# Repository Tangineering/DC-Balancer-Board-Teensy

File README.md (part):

# Scale_Car_Teensy

Teensy 4.1 firmware for a scale FCHEV (Fuel-Cell Hybrid EV) platform — the **Scale Car DC
Balancer Board, Rev 20260622**.

The board is a bidirectional power-pathing balancer: ideal-diode source switches route a fuel
cell and a 2S battery onto a shared VBUS, a regen path returns braking energy to the charger,
and an MPPT module harvests into the battery. This firmware drives that hardware.

It controls:
- motor torque through a VESC (`VescUart` over UART),
- fuel-cell/battery power sharing through dual AD5443 MDAC droop outputs (SPI),
- the RT1987 ideal-diode power-path switches (6 sequenced GPIOs),
- the Silvertel **Ag105** MPPT battery charger (I2C config + `MPPT_DISABLE` GPIO),
- the BQ29200 cell OVP/balancer (`CBAL_DISABLE` GPIO),
- command/telemetry with a Raspberry Pi over UDP Ethernet,
- a safety state machine, Pi watchdog, latching fault handling, and a USB-serial test mode.

> The authoritative hardware sources are `references/Scale Car Teensy IO - IO.csv` (pin map),
> `references/Scale Car Design PCB BOM 20260622.csv` (parts), and the schematic PDF. See
> `CLAUDE.md` for the reconciliation spec and `PLAN.md` for the implementation plan. For
> hardware-in-the-loop testing (a bare Teensy against a simulated plant, no PCB needed), see
> `docs/HIL_MODE.md` (protocol/architecture) and `docs/HIL_USER_MANUAL.md` (operator manual).

## Hardware interfaces

- **UART (`Serial1`)**: VESC motor controller (`RX`=0, `TX`=1).
- **SPI**: two AD5443 MDACs (`CS_MDAC_FC`=36, `CS_MDAC_BT`=37) for FC/BT droop gains; OPA197
  output buffers run from the 5 V rail (hardware bodge).
- **I2C (`Wire`)**: Silvertel **Ag105** charger at address **0x30**.
- **Ethernet/UDP**: command in (port 5001), telemetry out (port 5000), Teensy IP 192.168.1.50.
- **Encoder interrupts**: wheel-speed estimation from `ENC_A`=14 / `ENC_B`=15 (bodged from 2/8 on
  2026-08-16; the optical sensors are hardwired to power, so there is no enable pin).
- **ADC inputs (12-bit)**: FC/BT current (INA253A1, 0.1 V/A), FC/BT/BUS/CHG/RGN voltages.
- **Digital outputs**: FC/BT boost enables, 6 RT1987 path switches, `MPPT_DISABLE`,
  `CBAL_DISABLE`, encoder enable.

### Power-path switches (RT1987 ideal-diode controllers)

| Pin | Name | Role |
|----|------|------|
| 27 | `FC_BUS_ENABLE` | FC regulator → VBUS |
| 28 | `BT_BUS_ENABLE` | BT regulator → VBUS |
| 29 | `MOT_PWR_ENABLE` | VBUS → VESC/motor (Run only) |
| 30 | `REGEN_ENABLE` | regen → charger input |
| 31 | `FC_CHARGE_ENABLE` | VBUS(FC) → charger (guarded) |
| 32 | `BT_SEQUENCE_ENABLE` | battery-pack sequencing (init LOW, then HIGH) |

All switches default LOW at boot (fail-safe; 10 kΩ EN-to-GND bodge resistors back this up).
`FC_CHARGE_ENABLE` and `REGEN_ENABLE` are **mutually exclusive** and are only ever driven
through `assertFcChargeEnable()`, which forces `BT_BUS_ENABLE` and `REGEN_ENABLE` LOW (with an
RT1987 turn-off settle delay) before opening the FC→charger path.

**VBUS bring-up — only enable a boost on a stiff source.** The hazard is *not* bus inrush: VBUS
carries only ~30–40 µF (the RT1987 ceramics); the 470 µF bulk cap is on the V-MOT/regen node behind
`MOT_PWR_ENABLE`. The real failure mode is enabling a boost on a source that can **collapse**:
switching with built-up inductor current on a sagging/recovering rail destroys the power stage. The
exact mechanism is **unconfirmed pending a scope capture** — most likely a VOUT overshoot past the
20 V SW/VOUT abs-max (the TPS61288 OVP is at 19 V, only ~0.5 V of margin, and the 3×22 µF output
caps DC-derate to ~30 µF) and/or transient reverse conduction. Either way the destructive energy
comes from the boost's own inductor/output cap, so *a supply current limit does not bound it*. On a
board-powered Teensy this also motorboats: the boost loads `VBT`, the logic rail browns out, the MCU
resets, and re-enables the boost. So in **production** (`BENCH_TEST=0`, stiff vehicle source) State 0
brings the bus up gently (switches first, then the boosts' own soft-start) and is mirrored by the
State 98 `G` command; the bus is then kept energized through Idle/Finish so a Run never re-hot-plugs
it. Under **`BENCH_TEST`** State 0 keeps the power stage **off** at boot (see State 0 below). Bench
rule: the supply must exceed the logic baseline (≥ ~0.5–1 A) or the board-powered Teensy browns out,
and the bus may be brought up (`G`) only on a stiff supply.

## Runtime flow

Main loop execution order:
1. `updateSensors()`
2. `computeDerivedSignals()`
3. `detectFaults()`
4. `checkPiWatchdog()`
5. `receiveCommands()`
6. state machine (`doState0/1/2/3/98/99`)
7. `pollAg105()` + `sendTelemetry()` at ~50 Hz

## State machine

- **State 0 (Init)**: behavior depends on the `BENCH_TEST` build flag.
  - **Production (`BENCH_TEST=0`)**: a **non-blocking phase machine** that brings VBUS up gently —
    bus switches first (`FC_BUS_ENABLE`/`BT_BUS_ENABLE`), settle, then the FC/BT boosts (their
    soft-start raises the bus; see *VBUS bring-up* above). Raises `BT_SEQUENCE_ENABLE`, inits the
    MDAC and VESC, then **gates the transition to Idle on `V_bus ≥ V_BUS_CHARGED_THRESH`**; if the
    bus never reaches it within `BUS_CHARGE_TIMEOUT_MS`, raises `FAULT_INIT_FAIL` → State 99
    (catches a dead boost, failed switch, or no source).
  - **Bench (`BENCH_TEST=1`, the default flash)**: boots **straight to Idle with the power stage
    OFF** — boosts, bus switches, and `BT_SEQUENCE` all stay LOW, and there is no `V_bus` gate. This
    prevents enabling a boost on a soft/current-limited bench supply (which browns out the
    board-powered Teensy and motorboats the boost to failure). Bring the bus up manually with the
    State 98 `G` command on a stiff supply.
  - Either way the Ag105 is **not** configured here — it is unpowered in Init; `pollAg105()`
    configures it lazily once a charger path powers it. Shared init lives in `initControlPeripherals()`.
- **State 1 (Idle)**: motor current zero, `MOT_PWR_ENABLE` LOW; the bus is left **energized**
  (boosts + bus switches stay ON). Waits for a Run command from the Pi, or `T` on USB serial to
  enter test mode (State 98).
- **State 2 (Run)**: `MOT_PWR_ENABLE` HIGH; run `chargingControl()`, `motorControl()`,
  `powerBalance()`. `chargingControl()` owns the `REGEN`/`FC_CHARGE`/`BT_BUS` switches and the
  `MPPT_DISABLE` line. The bus is already up from Init/Idle, so entering Run does not hot-plug it.
- **State 3 (Finish)**: stops the motor and closes the motor/regen/charge paths, but **leaves the
  boosts + bus switches ON** so the bus stays armed and the next Idle→Run never re-hot-plugs the
  470 µF bus. Clears the wheel-speed buffer and returns to Idle. (No cap/regen drain — the
  disabled-boost back-feed hazard doesn't apply while the boosts stay enabled.)
- **State 98 (Test)**: USB-serial hardware exerciser (see below).
- **State 99 (Error)**: **non-blocking** two-phase safe shutdown that bleeds VBUS/regen energy and
  then disables the boosts and tears the bus down — latched until power cycle (which re-runs the
  State-0 gentle bring-up).

The State 99 shutdown is a phase machine gated on `millis()` (no blocking `delay()`), so
`detectFaults()` keeps sampling through the highest-energy drain windows.

## Charger control (Silvertel Ag105)

There is **no charge-current register to program per-mA**. Control is:
- **I2C config is LAZY, not at init** (`pollAg105()`): the charger is unpowered in
  Init/Idle (no charger power path is open, so it cannot ACK I2C), so reg `0x00 = 0x01`
  (2.5 A profile) and reg `0x01 = 0x08` (2S / 8.4 V) are written the first time
  `chargerHasPower()` is true and the `AG105_SETTLE_MS` bring-up window has elapsed and
  the charger ACKs. Stored in EPROM; the flag re-arms on power loss, so writes are
  idempotent. **fw v24** adds a dynamic reg `0x02` MPPT input-voltage threshold, written
  through the same power-gated lazy path with a read-verify-write handshake and an
  EPROM-wear write-rate budget.
- **`MPPT_DISABLE` GPIO (pin 5, active-LOW)**: LOW inhibits the MPPT loop (during regen,
  so it doesn't fight the fast transient); HIGH releases it (cruise/coast harvest). The
  Ag105's MPPT mechanism is an **input-voltage-threshold regulator** (datasheet p.10),
  not perturb-and-observe — charging commences only once the input exceeds a threshold
  set by reg `0x02` (11–33 V, ~0.088 V/count; default 18 V with no MPPTS resistor
  fitted).
- **I2C polling** (`pollAg105()` at 50 Hz): reads reg `0x06` (measured charge current,
  0.011 A/count) into `I_charge`, and caches the Table-6 status byte. The Ag105 prepends its
  status byte before any read, so each 1-byte field is read as 2 bytes.
- **Readiness** (`ag105IsReady()`): GENSTAT (status bits [2:0]) == Charging (0x02) or
  Fully Charged (0x03).
- An Ag105 I2C read failure only latches State 99 in the charging-relevant states (Run/Finish);
  in Init/Idle/Test a missing or still-powering charger does not lock the system.

## Telemetry & commands

- **Commands**: 22-byte UDP packet (sync `0xBB` + XOR checksum). Fields: timestamp, counter,
  `v_setpoint`, `power_share_setpoint`, `charge_goal`, `mode_cmd`, and a reserved `droop_enable`
  byte (parsed, not yet wired).
- **Telemetry — protocol v4, 58 bytes** (`TELEMETRY_VERSION = 4`, sync `0xAA`, XOR over bytes
  1–56). Carries the measured/derived signals, droop gains, the raw Ag105 Table-6
  `charger_status` byte (offset 51), a `switch_state` bitmask of the 6 path switches, a 16-bit
  `fault_flags`, the latched `error_code`, and `error_source_state`. The Pi bridge parses fixed
  offsets and **must match this version** — see `PLAN.md` §6b for the byte-by-byte layout and the
  block comment above `sendTelemetry()`.

## Key functions

### `motorControl()` + `PI_Controller_Motor()`
Computes torque from speed error (`v_setpoint - v_actual`) and commands VESC current. The
integrator has **anti-windup**: `pi_motor_accum` is clamped to the torque equivalent of
`MOTOR_I_CMD_MAX`. Integrator state is file-scope (resettable by the unit tests).

### `powerBalance()` + `PI_Controller_Power()`
Controls the FC/BT split from measured INA253 currents; PI output (`droopRatio`) is mapped to
FC/BT droop gains and written via `setDroopMdac()` (AD5443, SPI_MODE0, MSB-first, `transfer16`).

### `chargingControl()`
Manages `MPPT_DISABLE` and the regen/FC-charge/BT-bus switches based on `charge_goal`, regen
state (`current < -0.1`), and Ag105 readiness — enforcing the FC-charge/regen mutual exclusion.

### `updateWheelSpeed()` + encoder ISRs
An **edge-period estimator** (fw v12, hardened by the fractional-pitch ledger in fw v15/v17)
measures the period between same-edge-type quadrature transitions to derive flywheel speed →
`v_actual`. It replaced the original boxcar (fixed-window sample-counting) estimator, whose
~113 ms window realized enough group delay to limit-cycle the drive loop at its own crossover.
Direction comes from the quadrature decode; a ring-invalidation event on a direction flip
holds the last valid reading (bounded by a stale timeout) rather than emitting a full-scale
zero step. State 3 resets the estimator between runs so a new run's first samples aren't
measured against stale timestamps.

## Safety features

- FC overcurrent (`I_fc > LIMIT_I_FC_MAX`), BT overcurrent (`I_batt > LIMIT_I_BT_MAX`)
- Battery UV/OV, FC UV — **UV checks are gated to Run (State 2)** so unramped rails at boot
  don't latch State 99
- Bus OV (`LIMIT_V_BUS_MAX = V_BUS_NOMINAL + 1.5 = 17.5 V` at the 16.0 V nominal, below the 19 V TPS61288 HW OVP) and Bus UV (Run only)
- Regen-node and charger-input overvoltage
- Illegal switch combination (`FC_CHARGE_ENABLE` with `BT_BUS`/`REGEN`)
- Ag105 GENSTAT error states (OC/Regulation 0x05, Thermal Shutdown 0x06, Timeout 0x07) and I2C
  comms failure
- Pi watchdog timeout (`PI_TIMEOUT_MS`, States 2/3 only)

Faults funnel through `triggerFault()`, which latches a primary `error_code` + source state and
transitions to **State 99**.

## Fault reference

When any check in `detectFaults()` trips, `triggerFault()` sets that condition's bit in the
16-bit `fault_flags`, latches the **first** cause into `error_code` (and the active state into
`error_source_state`), forces `FAULT_ERROR` (`0x8000`), and transitions to **State 99** —
latched until power cycle. Both `fault_flags` and `error_code` ride in the v4 telemetry packet,
so every value below is observable on the Pi. Read `error_code` for the root cause and
`fault_flags` for everything that tripped.

### Fault flags (`fault_flags` bitmask)

`fault_flags` is an OR of these bits — more than one can be set at once:

| Mask | Flag | Trigger | Limit | Gated to |
|------|------|---------|-------|----------|
| `0x0001` | `FAULT_OC_FC` | `I_fc` overcurrent | `LIMIT_I_FC_MAX = 3.5 A` | all |
| `0x0002` | `FAULT_UV_BATT` | `V_batt` undervoltage | `LIMIT_V_BATT_MIN = 6.2 V` | Run |
| `0x0004` | `FAULT_OV_BUS` | `V_bus` overvoltage | `LIMIT_V_BUS_MAX = 17.5 V` | all |
| `0x0008` | `FAULT_SWITCH_CONFLICT` | `FC_CHARGE_ENABLE` high while `BT_BUS`/`REGEN` high | — | all |
| `0x0010` | `FAULT_PI_TIMEOUT` | Pi watchdog expired | `PI_TIMEOUT_MS` | States 2/3 |
| `0x0020` | `FAULT_OV_BATT` | `V_batt` overvoltage | `LIMIT_V_BATT_MAX = 8.6 V` | all |
| `0x0040` | `FAULT_UV_FC` | `V_fc` undervoltage | `LIMIT_V_FC_MIN = 6.0 V` | Run |
| `0x0080` | `FAULT_OC_BT` | `I_batt` overcurrent | `LIMIT_I_BT_MAX = 6.0 A` | all |
| `0x0100` | `FAULT_UV_BUS` | `V_bus` undervoltage | `LIMIT_V_BUS_MIN = 12.0 V` | Run |
| `0x0200` | `FAULT_OV_RGN` | regen-node overvoltage | `LIMIT_V_RGN_MAX = 28.0 V` | all |
| `0x0400` | `FAULT_OV_CHG` | charger-input overvoltage | `LIMIT_V_CHG_MAX = 24.0 V` | all |
| `0x0800` | `FAULT_I2C_CHARGER` | Ag105 I2C comms failure | — | Run/Finish |
| `0x1000` | `FAULT_CHARGER_STAT` | Ag105 GENSTAT error (`0x05` OC/regulation, `0x06` thermal, `0x07` timeout) | — | charging states |
| `0x2000` | `FAULT_INIT_FAIL` | init failure: VBUS failed to reach `V_BUS_CHARGED_THRESH` within `BUS_CHARGE_TIMEOUT_MS` (also legacy Ag105 config) | `V_BUS_CHARGED_THRESH` | State 0 |
| `0x8000` | `FAULT_ERROR` | latched marker: system entered State 99 | — | set with any fault |

The UV checks marked **"Gated to Run"** are deliberately suppressed outside State 2, so unramped
rails at boot don't latch State 99 (see Safety features above).

### Error codes (`error_code` latched cause)

`error_code` is the single latched primary cause — the *first* fault to fire — and is distinct
from the multi-bit `fault_flags`. `error_source_state` records which state was active when it
latched. Values map 1:1 to `errorCodeStr()`:

| Code | Enum | String |
|------|------|--------|
| `0x00` | `ERR_NONE` | (none) |
| `0x01` | `ERR_OC_FC` | FC overcurrent |
| `0x02` | `ERR_UV_BATT` | Batt undervoltage |
| `0x03` | `ERR_OV_BUS` | Bus overvoltage |
| `0x04` | `ERR_SWITCH_CONFLICT` | Switch conflict |
| `0x05` | `ERR_PI_TIMEOUT` | Pi timeout |
| `0x06` | `ERR_OV_BATT` | Batt overvoltage |
| `0x07` | `ERR_UV_FC` | FC undervoltage |
| `0x08` | `ERR_OC_BT` | BT overcurrent |
| `0x09` | `ERR_UV_BUS` | Bus undervoltage |
| `0x0A` | `ERR_OV_RGN` | Regen overvoltage |
| `0x0B` | `ERR_OV_CHG` | Charger input OV |
| `0x0C` | `ERR_I2C_CHARGER` | Ag105 I2C fail |
| `0x0D` | `ERR_CHARGER_STAT` | Ag105 STAT fault |
| `0x0E` | `ERR_INIT_FAIL` | Init failure |

**Recovery:** State 99 is latched — a fault clears only on a power cycle. Diagnose with
`error_code` (root cause) first, then inspect the full `fault_flags` bitmask for any secondary
conditions that tripped in the same tick.

## Test mode (State 98)

State 98 is a USB-serial hardware exerciser for bench bring-up. **Enter** it by sending `T`
while in Idle (State 1); **exit** with `Q`, which returns to Idle and forces `MOT_PWR_ENABLE`
LOW. The Pi watchdog is suspended in this state, but `detectFaults()` still runs every tick — a
fault latches State 99 exactly as in normal operation. `FC_CHARGE_ENABLE` only ever moves through
`assertFcChargeEnable()`, even here.

### Serial command set

All commands are single characters over USB serial; every toggle echoes the resulting pin state
back over serial:

| Key | Action | Notes |
|-----|--------|-------|
| `F` | Toggle `FC_REG_ENABLE` (FC boost) | |
| `B` | Toggle `BT_REG_ENABLE` (BT boost) | |
| `1` | Toggle `FC_BUS_ENABLE` | **ON refused** if FC boost is ON and `V_bus` < `V_BUS_CHARGED_THRESH` (hot-plug guard — use `G`) |
| `2` | Toggle `BT_BUS_ENABLE` | same hot-plug guard as `1`; **also refused** while `FC_CHARGE_ENABLE` is HIGH (illegal combination) |
| `3` | Toggle `MOT_PWR_ENABLE` | ON allowed **only at a regulated bus** (`motPwrConnectBlocked()`); must be HIGH before `D`/`R` |
| `4` | Toggle `REGEN_ENABLE` | forces `FC_CHARGE` off via `assertFcChargeEnable(false)` before going HIGH |
| `5` | Toggle `FC_CHARGE_ENABLE` | always through the `assertFcChargeEnable()` guard |
| `6` | Toggle `BT_SEQUENCE_ENABLE` | |
| `C` | Toggle `CBAL_DISABLE` | HIGH = OVP bypassed (prints a warning) |
| `M` | Toggle `MPPT_DISABLE` | HIGH = MPPT harvesting; LOW = inhibited |
| `N` | Dynamic Ag105 MPPT reg-`0x02` threshold status/verify (fw v24) | read-verify-write handshake against the EPROM-wear write-rate budget; see `CLAUDE.md`'s 2026-09-01a addendum |
| `G` | Staged bus bring-up | `busBringupTick()` phases P0–P3: bus alone → boosts → dwell → motor node; `X` aborts (stage dark) |
| `D` | Start/stop simulated drive cycle | requires `MOT_PWR_ENABLE` HIGH and the calibrated velocity chain |
| `S` | Print status dump (all pins, ADCs, `I_charge`, faults, bench-tool state) | read-only |
| `I` | Scan the I2C bus | read-only |
| `E` | One-shot VESC firmware + telemetry read | blocks up to ~100 ms (bench-only) |
| `U` | Toggle VESC watch (~2 Hz `[VW]` line, flags fault changes) | **rebound from `W` (2026-08-10)**; auto-paused during profiles and plot mode |
| `P` | Set power-share setpoint (prompts for a value) | closed-loop: `powerBalance()` drives the MDACs live; needs current flowing |
| `O` | Set droop ratio 0.15–0.85 (prompts for a value) | open-loop direct MDAC write; no current needed — the calibration entry point |
| `A` | Set manual motor current in A (prompts) | constant VESC current, bypasses the drive controller |
| `V` | Set manual motor velocity in m/s (prompts) | refused until the velocity chain is calibrated |
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
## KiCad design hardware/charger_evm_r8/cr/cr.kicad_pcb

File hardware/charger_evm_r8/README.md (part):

# Charger EVM r9: design review guide

## 1. Purpose and how to read this document

This README presents the r9 charger design for operator review, with progressive detail. Section 2 shows the overall
functional block diagram and the architecture. Section 3 lists what changed on 2026-11-12; a reader who needs only the
changes can read section 3 alone. Sections 4 to 7 explain the design concepts, the permit gate, the operating modes and the
firmware consequences. Sections 8 to 12 cover the physical implementation, status, plan, open items and the source
index. Appendix A defines the abbreviations and the identifier families.

The full record is the design document `docs/charger_bq25798_wiring_design_2026-11-05.md` (revision r9). Section 12 maps
each topic to its authoritative file and section. Neither text that the design document marks "superseded", "withdrawn"
or "history" nor the r7-outline work in `archive_r7_outline/` is the current design.

## 2. Architecture

### 2.1 Block diagram

Three different parts carry the refdes J1. In this document, **CR J1** is the 22-pin CHG header (TSW strips). **MB
J1/J2** are the Teensy 4.1 Dubox receptacles, and **EVM J1** is the charger VIN screw terminal.

Figure 2.1 shows the power and signal architecture of the charger path. Power flows from VBUS or V-MOT into the EVM and
returns to the pack through CR J1 pads 18/19.

Figure 2.1. Charger path, block diagram (r9).

The diagram is schematic and not to scale. Thick red conductors carry power and thin blue lines carry logic or analog
signals; a bridge marks a crossing with no connection. The source is `gen/readme_figures.py`. Only CR J1 pad 11 and the J-TAP conductors enter the permit gate. Table 2.2, section 8.6 and
design-document sections A.5 and C give the EIB-to-EVM leads and the EVM modifications.

### 2.2 Blocks

Table 2.1 lists each block, its role and its physical location.

Table 2.1. Blocks of the charger path.

| Block | Role | Physical location |
|---|---|---|
| MB RT1987 switches D-BC-FC, D-BC-RG | Route VBUS (FC charging) or V-MOT (regen) into VCHG-IN | MB, existing parts |
| MB D-BT-SQ (RT1987) | Connects the charger output net VCHG to the pack VBT | MB, existing part |
| CR J1 (22-pin CHG header) | Mates the CR to the 22 former Ag105 holes | CR underside, TSW strips in MB SSQ sockets |
| eFuse U101 TPS26630RGER | Input current limit 2.23 A nominal, UVLO 9.91 V, OVP 23.12 V; fault output and IMON | CR top |
| Permit gate | Four comparators and five LVC packages; holds the converter off unless a release term is true | CR top |
| J-TAP (J102) | Brings the ten tap conductors onto the CR | CR, THT header, +x side |
| EVM (BQ25798) | Buck-boost charger, I2C address 0x6B | Off-board, on an insulating plate fixed to the chassis |
| EIB | Converts CR logic levels into /CE, ILIM_HIZ hold/release and the FC current clamp at the EVM | 2-layer board on two M3 x 10 mm nylon standoffs on the EVM plate |
| Teensy 4.1 | Commands CHG_ARM, CHG_QUAL and the RT1987 enables; reads readbacks and I2C | MB, on J1/J2 receptacles |

Every block in Table 2.1 appears in Figure 2.1. Only the MB switches, the eFuse and the EVM carry charger power; the
other blocks carry logic.

### 2.3 Interfaces

Table 2.2 lists each interface, its connector and what crosses it.

Table 2.2. Interfaces of the charger path.

| Interface | Connector | What crosses it |
|---|---|---|
| MB to CR power and signals | MB SSQ-110/112-01-L-S sockets, CR TSW-110/112-07-L-S strips (CR J1) | Pad 10 VCHGIN; pads 18/19 VCHG; pads 4, 14, 15 GND; pad 11 CHG_ARM; pad 3 STAT; pads 8/7 SDA/SCL; pad 13 TS_EXT; 11 pads without a net |
| MB to CR taps | J-TAP (J102) Micro-Fit 3.0 2 x 5 (Molex 43045-1012), cable Molex 2147561101 | T1, T7b, T2, T5, T6, T10, T13, T16, T17, T17r |
| CR to EVM input | W1 (VCHGOUT), W2 (GND); CR plated holes to EVM J1 screw terminal | Charger input, <= 2.41 A for <= 202 ms (eFuse limit), normally <= 1.76 A |
| EVM to CR output | W3 (VCHG), W4 (GND); EVM J5 screw terminal to CR plated holes | Charger output, <= 3.21 A |
| CR to EVM I2C | W7 twisted triple; CR plated holes to EVM J8 (Molex KK 254 housing) | SCL, SDA; GND bonded at the CR end only |
| CR to EVM thermistor | W6 twisted pair to EVM J7 pin 1 | TS_EXT; fitted only if a pack NTC is fitted at J-NTC |
| CR to EIB | W5 14-way 0.635 mm flat cable, CR J101 to EIB J201 | 3V3 (two conductors), CE_DRV, ILIM_REL_A, ILIM_REL_B, RFC_OFF to the EIB; STAT to the CR; four GND |
| EIB to EVM | E leads, 28 AWG Kynar | E8 AGND to TP49, E3 to TP33, E2 to JP14 pin 2, E7 STAT to TP38, E1 REGN to JP12, E5 /CE to TP36 |

Every interface in Table 2.2 appears in Figure 2.1. The power interfaces are CR J1 pads 4, 10, 14, 15, 18 and 19 and the
leads W1-W4. All logic crosses CR J1, J-TAP, W5, W6, W7 or the E leads.

## 3. What changed on 2026-11-12

The thermocouple and the polyimide sheet are removed, T-F-16 is retired, and no charging of any kind runs before the R5 build flag
(section 7.2). Sections 3.1 to 3.3 give the full change record.

### 3.1 Physical and functional changes

The 2026-11-12 decisions removed parts, moved signals and replaced the carrier outline. Table 3.1 lists every change that
a reviewer could otherwise miss. The decision identifiers refer to `LAYOUT_DECISIONS.md` (D-38 to D-50) and to the
design-document change rows r8-17 and r9-1 to r9-8. The CR outline row and the standoffs row also give the 2026-11-13
outline trim and mounting holes of D-60, as amended by the D-62 outline. (**Superseded 2026-11-13, D-62:** "outline
trim and mounting holes of D-60.")

Table 3.1. Changes of 2026-11-12.

| Area | Before (r8 or r7) | Now (r9) | Record |
|---|---|---|---|
| Thermocouple on the MB VBT trace | Fitted under the polyimide sheet, read in T-F-16 | **Removed.** No replacement. The MB VBT trace, at its IPC-2221 10 C rise at 3.21 A on 1 oz, is accepted unmeasured; T-F-16 is retired (operator ruling 2026-11-12, design-document J.1 item 25) | D-43 |
| Polyimide sheet over 368 untented MB vias | 0.125 mm sheet bonded under the CR | **Retired.** Protection is the >= 1.5 mm air gap and the solder-masked L4 GND | D-43 |
| CR outline | r7 outline with tab X, tab Y, chamfer and feet FT1/FT2 | **Plug-on rectangle** x 18.584-67, y 7-94 (48.416 x 87 mm, 4212.2 mm2), removable; this rectangle stays the placement frame. 2026-11-13: after routing, the board is trimmed to the **D-62 outline** inside the rectangle: 10 corners, edges at 0, 30, 45, 60, 90, 120, 135 or 150 degrees, slanted edges of at least 2.0 mm, 1.0 mm corner fillets; 2327.7 mm2 (55 %), bounding box 40.02 x 64.81 mm, x 18.584-58.60, y 7.83-72.64. (**Superseded 2026-11-13, D-62:** "a **convex 18-vertex outline** inside the rectangle: 2241.6 mm2 (53 %) ... x 18.58-58.60", the D-60 trim.) | D-39, D-60, D-62 |
| MB parts under the CR | None of the switching parts | Both boost switching nodes, L-FC, L-BT, REG-5V: about 1.6-3.3 W, BT boost TODO(calc) (Table 8.1) | D-39 |
| MB-CR mating | TSW pins soldered into the MB | Samtec SSQ sockets on the MB, TSW strips on the CR, hard stop at 11.05 mm | D-41 |
| Standoffs, feet, key | Feet FT1/FT2 bonded with RTV | **No standoffs on the MB.** Friction fit of 22 contacts; J-BL and J-FC stop a flipped CR, and a +x key ear keeps that overlap; T-F-18 re-scoped to CR retention. 2026-11-13: four 6-32 NPTH holes MH1-MH4 on the CR hold a 3D-printed support. (**Superseded 2026-11-13, D-60:** "**None.**" and "the terminal blocks stop a flipped CR".) | D-41, D-42, D-60 |
| Assembly | SMT on both sides | **All SMT on the top**, one stencil, one reflow; THT hand-soldered last | D-44 |
| Copper weight | 2 oz outer / 1 oz inner | 1 oz outer / 0.5 oz inner (OSH Park); set on 2026-11-11, kept by the 2026-11-12 amendment | D-29 |
| L4 use | Signals, the VCHGOUT strap and a GND pour | Solid GND, no signals, no straps | D-20 |
| Finish method | Interactive finish from the r7 start board | Retired; full route-race on the new outline | D-36, D-50 |
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
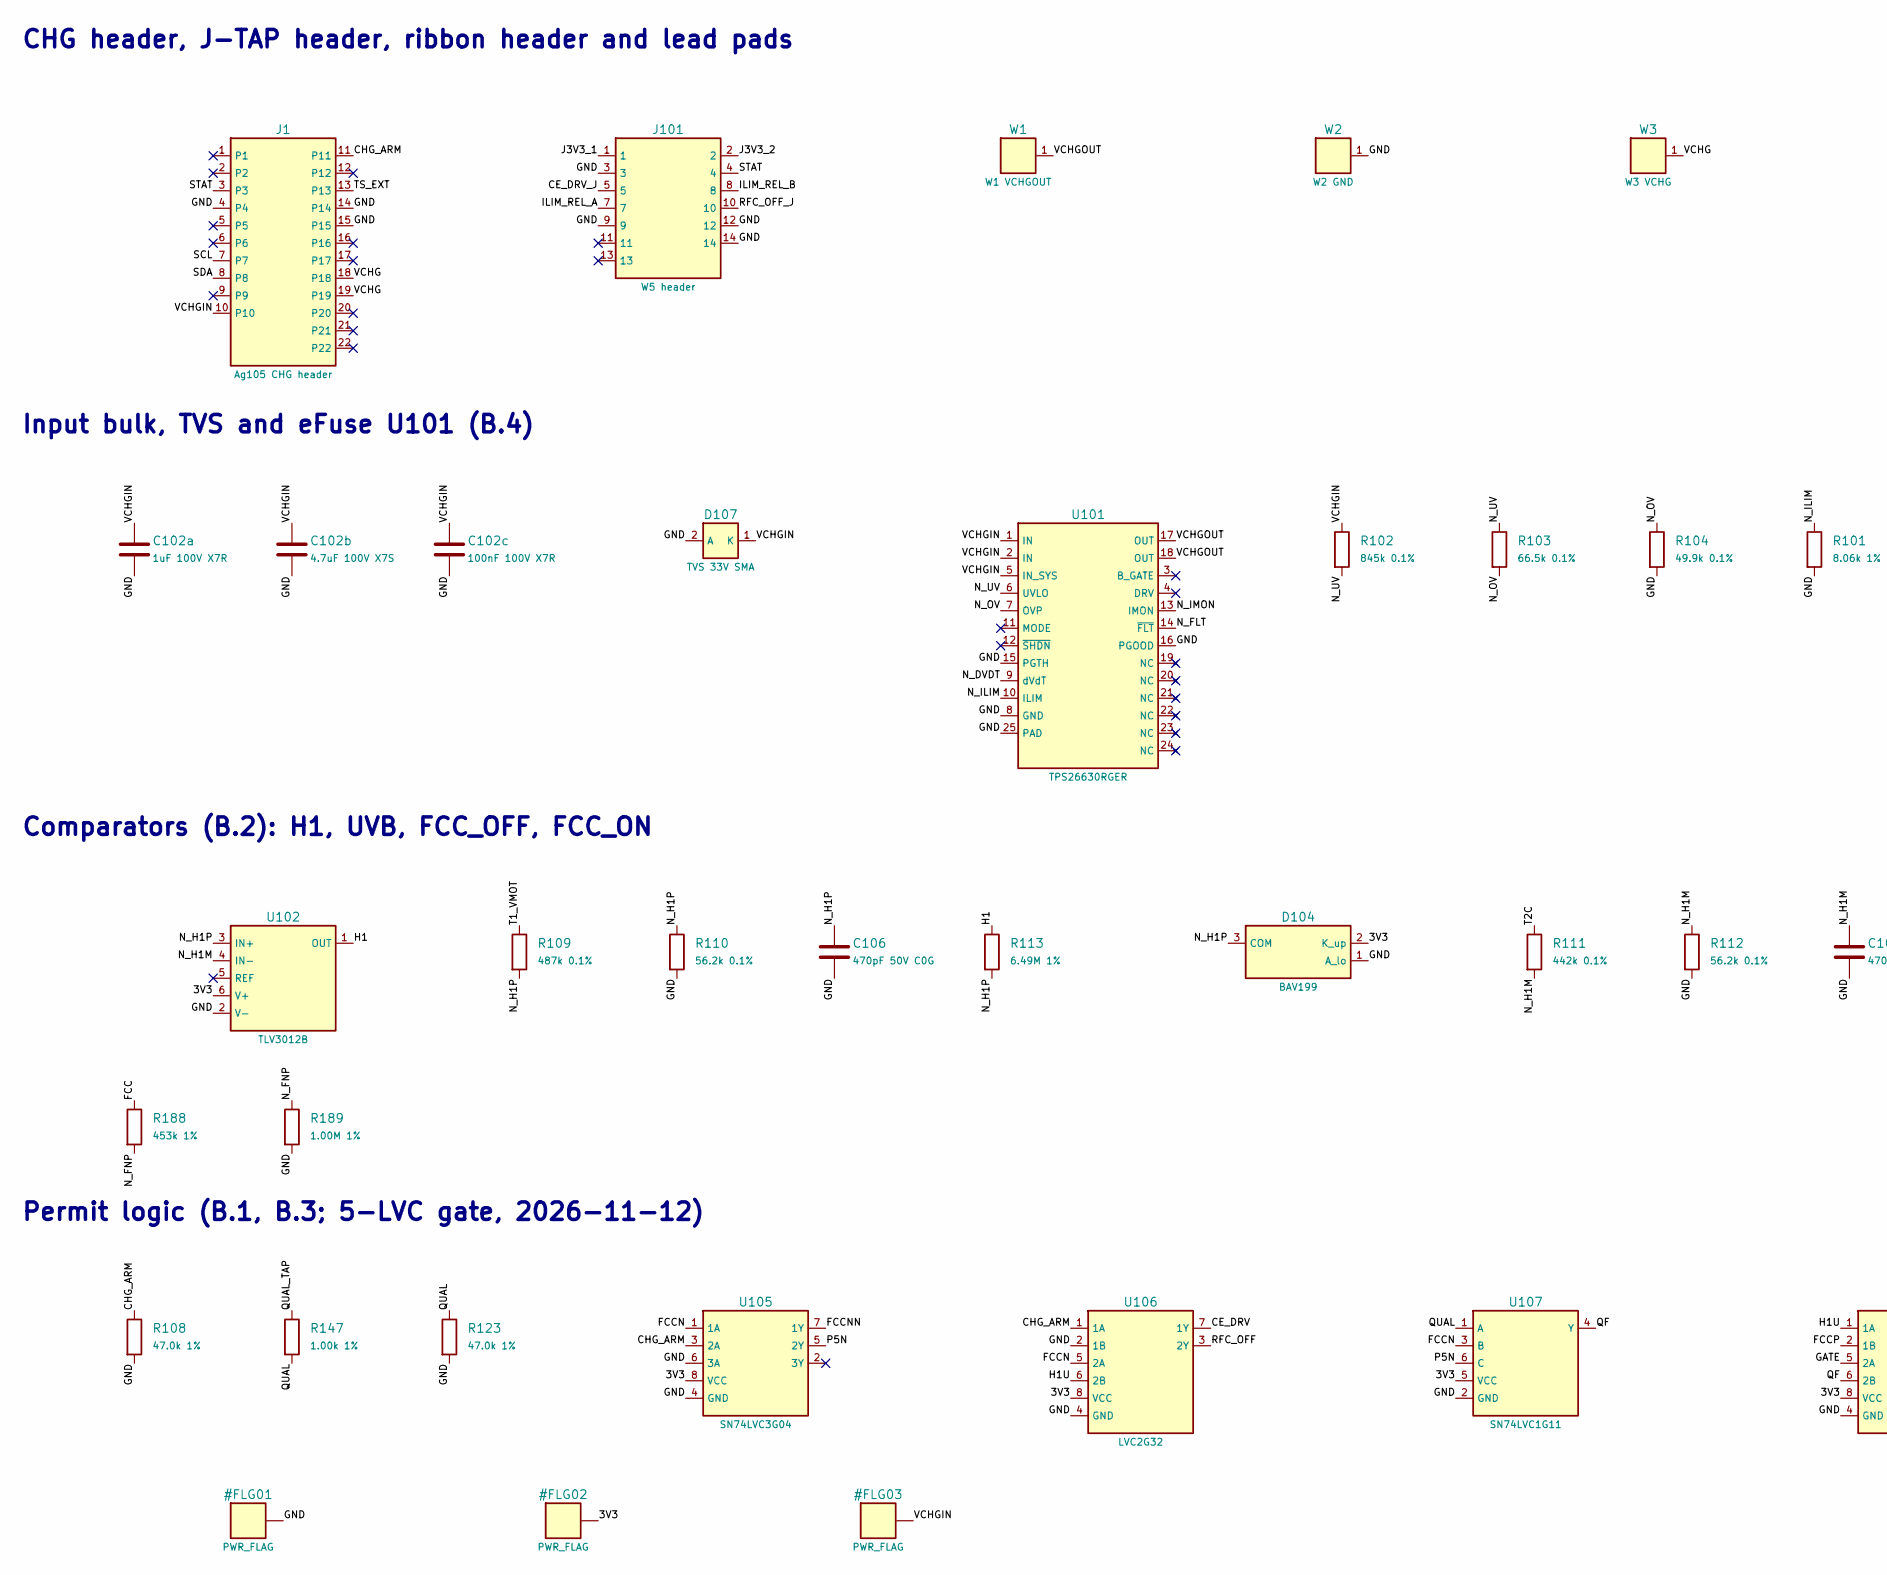
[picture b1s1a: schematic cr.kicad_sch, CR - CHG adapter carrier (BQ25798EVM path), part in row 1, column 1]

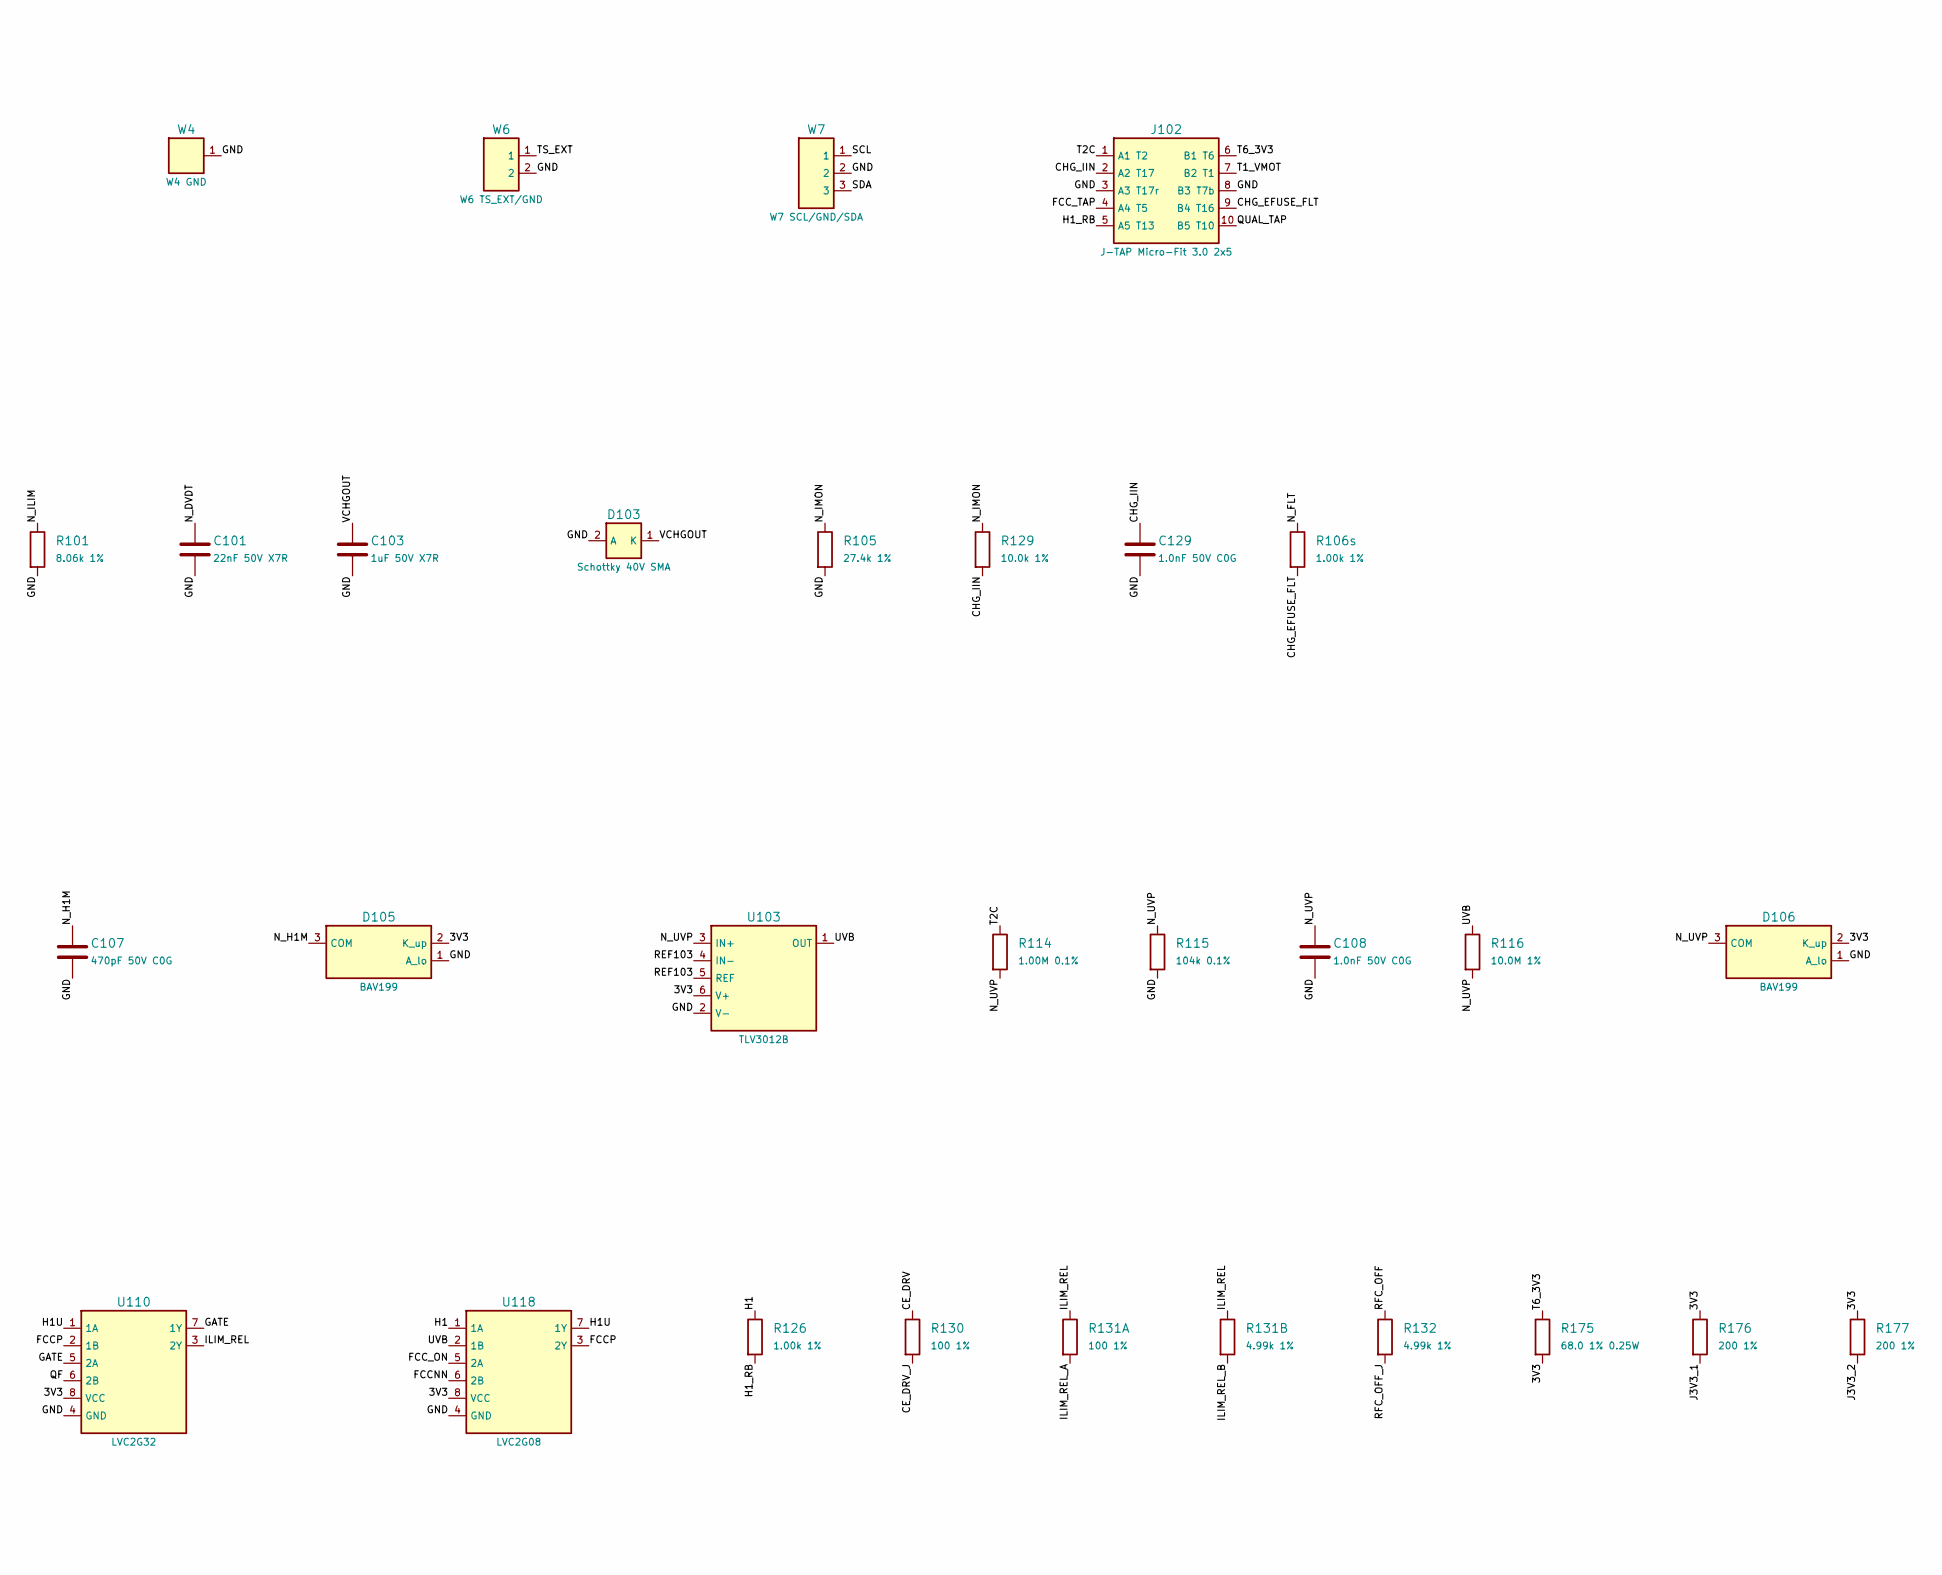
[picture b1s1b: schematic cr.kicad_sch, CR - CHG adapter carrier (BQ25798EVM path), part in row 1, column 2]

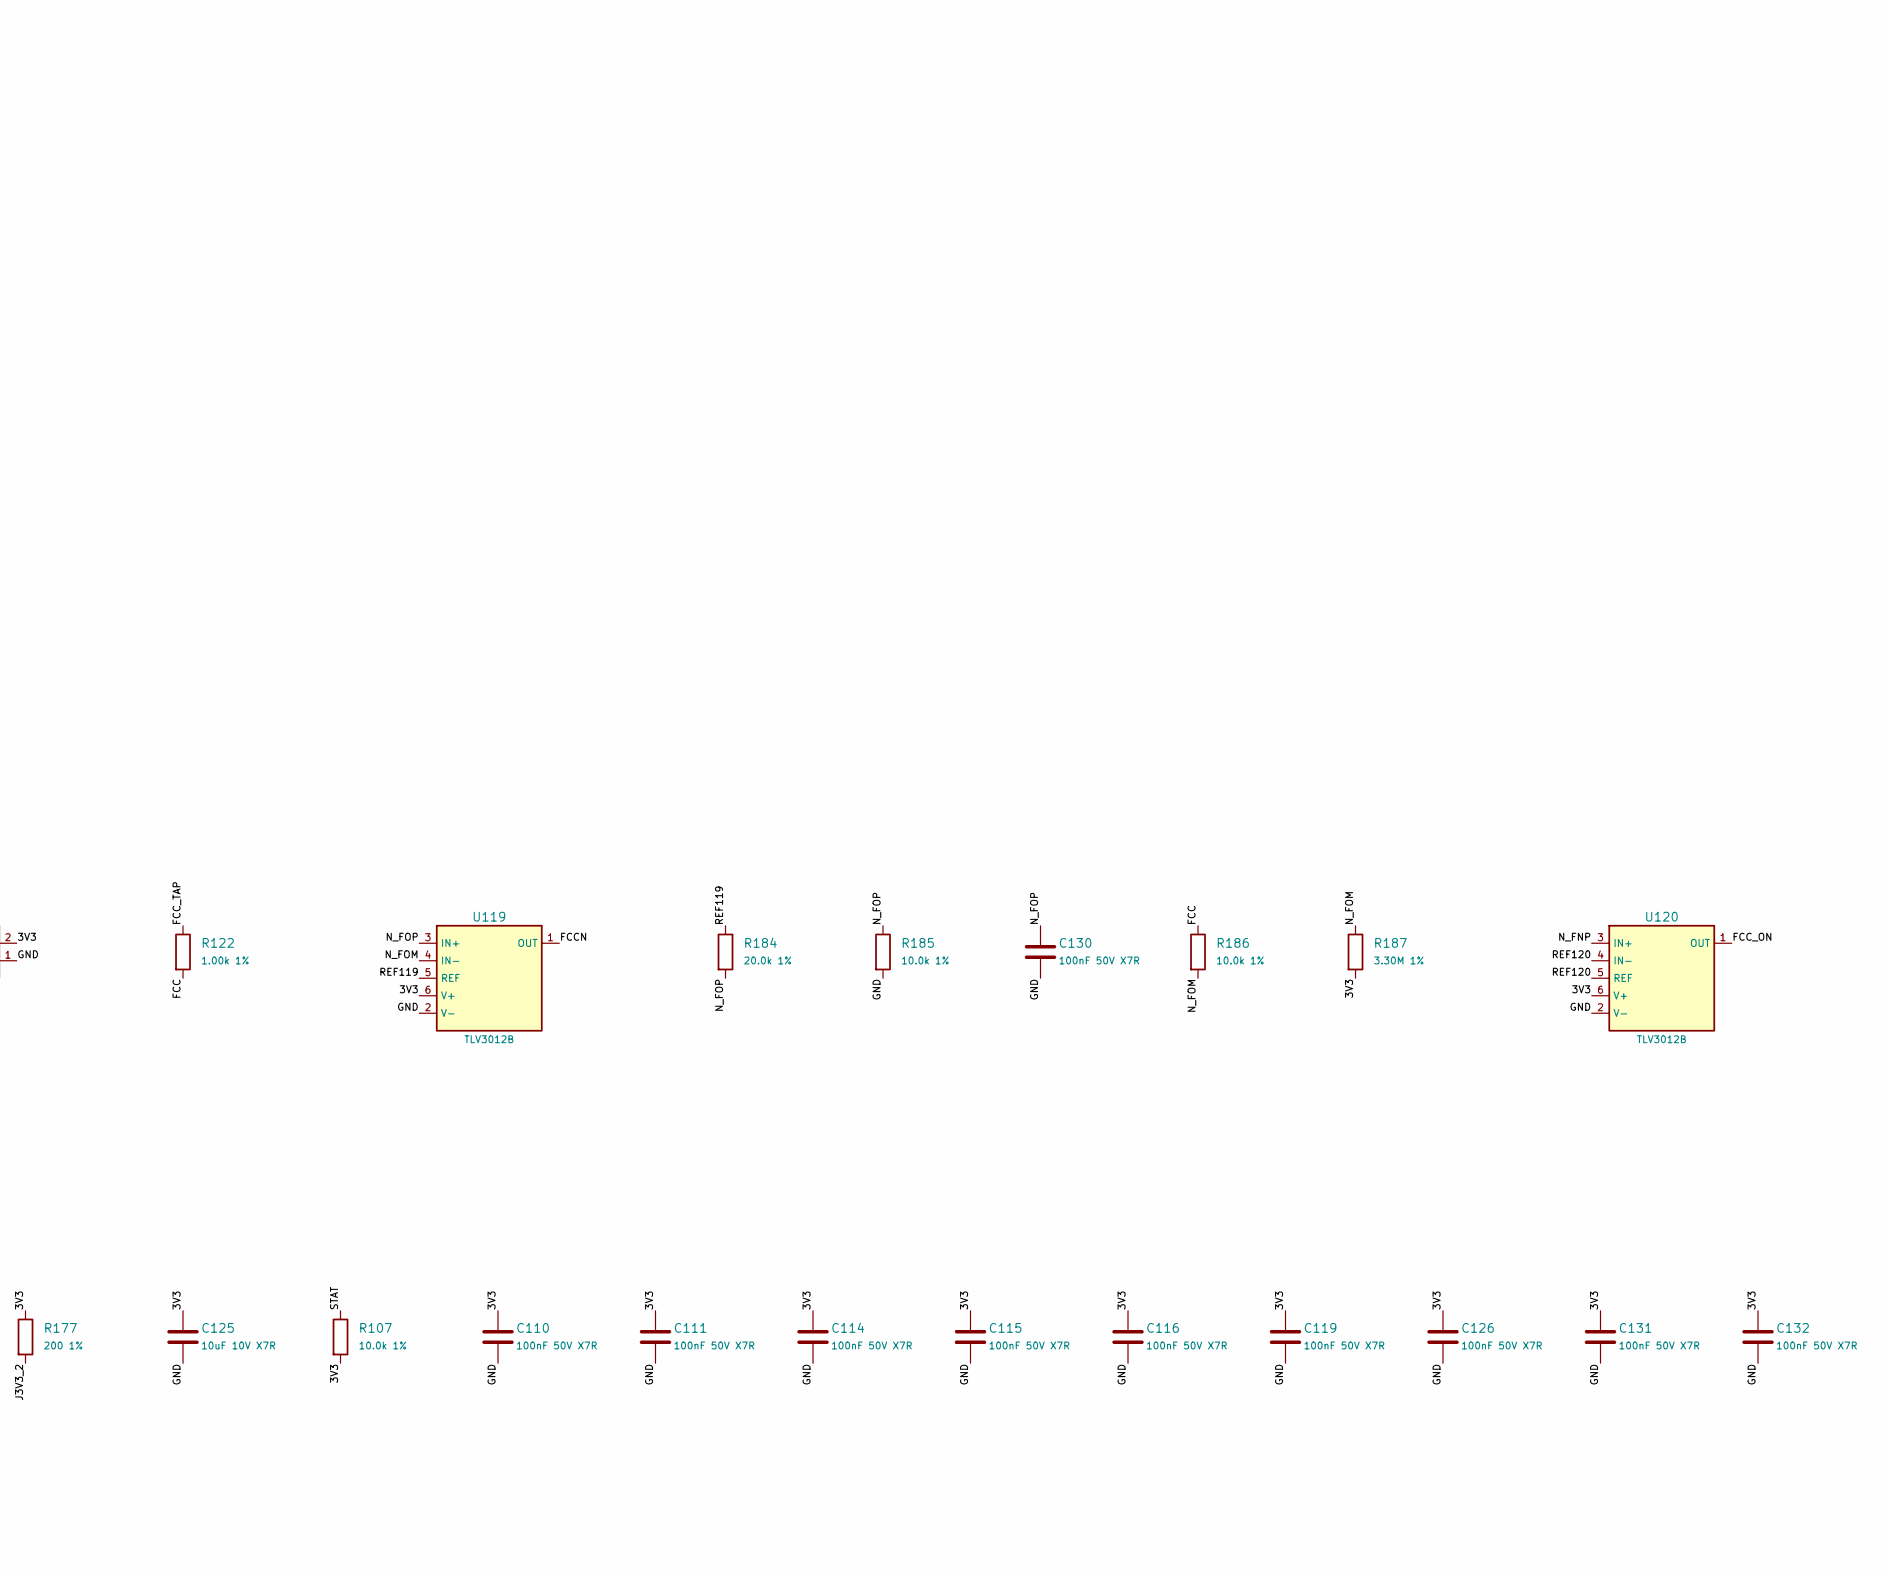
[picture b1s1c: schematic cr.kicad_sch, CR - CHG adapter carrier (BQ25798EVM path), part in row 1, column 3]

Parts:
C101: 22nF 50V X7R; C_0603_1608Metric_CrtYd0.25; MPN GRM188R71H223KA01D
C102a: 1uF 100V X7R; C_1206_3216Metric_CrtYd0.25; MPN GRM31CR72A105KA01L
C102b: 4.7uF 100V X7S; C_1210_3225Metric_CrtYd0.25; MPN C3225X7S2A475K
C102c: 100nF 100V X7R; C_0603_1608Metric_CrtYd0.25; MPN GRM188R72A104KA35D
C103: 1uF 50V X7R; C_0805_2012Metric_CrtYd0.25; MPN GRM21BR71H105KA12L
C106, C107: 470pF 50V C0G; C_0603_1608Metric_CrtYd0.25; MPN GRM1885C1H471JA01D
C108, C129: 1.0nF 50V C0G; C_0603_1608Metric_CrtYd0.25; MPN GRM1885C1H102JA01D
C110, C111, C114, C115, C116, C119, C126, C130, C131, C132: 100nF 50V X7R; C_0603_1608Metric_CrtYd0.25; MPN GRM188R71H104KA93D
C125: 10uF 10V X7R; C_0805_2012Metric_CrtYd0.25; MPN GRM21BR71A106KE51L
D103: Schottky 40V SMA; D_SMA_CrtYd0.25; MPN selected in T-A-05 (bench fallback B340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
D104, D105, D106: BAV199; SOT-23_CrtYd0.25; MPN BAV199,215
D107: TVS 33V SMA; D_SMA_CrtYd0.25; MPN SMAJ33A (candidate, T-A-05)
J1: Ag105 CHG header; Ag105_CHG_Carrier_22pin_P2.54mm; MPN TSW-110-07-L-S + TSW-112-07-L-S
J101: W5 header; Samtec_FTSH-107-01-DV_2x07_P1.27mm_SMD_NoPin6_CrtYd0.25; MPN FTSH-107-01-L-DV class (T-A-05)
J102: J-TAP Micro-Fit 3.0 2x5; Molex_Micro-Fit_3.0_43045-1012_2x05_P3.00mm_Vertical_CrtYd0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; MPN Molex Micro-Fit 3.0 2x5 THT header, 430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
R101: 8.06k 1%; R_0603_1608Metric_CrtYd0.25; MPN CRCW06038K06FKEA
R102: 845k 0.1%; R_0805_2012Metric_CrtYd0.25; MPN TNPW0805845KBEEA
R103: 66.5k 0.1%; R_0603_1608Metric_CrtYd0.25; MPN TNPW060366K5BEEA
R104: 49.9k 0.1%; R_0603_1608Metric_CrtYd0.25; MPN TNPW060349K9BEEA
R105: 27.4k 1%; R_0603_1608Metric_CrtYd0.25; MPN CRCW060327K4FKEA
R106s, R122, R126, R147: 1.00k 1%; R_0603_1608Metric_CrtYd0.25; MPN CRCW06031K00FKEA
R107, R129, R185, R186: 10.0k 1%; R_0603_1608Metric_CrtYd0.25; MPN CRCW060310K0FKEA
R108, R123: 47.0k 1%; R_0603_1608Metric_CrtYd0.25; MPN CRCW060347K0FKEA
R109: 487k 0.1%; R_0805_2012Metric_CrtYd0.25; MPN TNPW0805487KBEEA
R110, R112: 56.2k 0.1%; R_0603_1608Metric_CrtYd0.25; MPN TNPW060356K2BEEA
R111: 442k 0.1%; R_0805_2012Metric_CrtYd0.25; MPN TNPW0805442KBEEA
R113: 6.49M 1%; R_0603_1608Metric_CrtYd0.25; MPN CRCW06036M49FKEA
R114: 1.00M 0.1%; R_0805_2012Metric_CrtYd0.25; MPN TNPW08051M00BEEA
R115: 104k 0.1%; R_0603_1608Metric_CrtYd0.25; MPN TNPW0603104KBEEA
R116: 10.0M 1%; R_0603_1608Metric_CrtYd0.25; MPN CRCW060310M0FKEA
R130, R131A: 100 1%; R_0603_1608Metric_CrtYd0.25; MPN CRCW0603100RFKEA
R131B, R132: 4.99k 1%; R_0603_1608Metric_CrtYd0.25; MPN CRCW06034K99FKEA
R175: 68.0 1% 0.25W; R_1206_3216Metric_CrtYd0.25; MPN CRCW120668R0FKEA
R176, R177: 200 1%; R_0603_1608Metric_CrtYd0.25; MPN CRCW0603200RFKEA
R184: 20.0k 1%; R_0603_1608Metric_CrtYd0.25; MPN CRCW060320K0FKEA
R187: 3.30M 1%; R_0603_1608Metric_CrtYd0.25; MPN CRCW06033M30FKEA
R188: 453k 1%; R_0603_1608Metric_CrtYd0.25; MPN CRCW0603453KFKEA
R189: 1.00M 1%; R_0603_1608Metric_CrtYd0.25; MPN CRCW06031M00FKEA
U101: TPS26630RGER; TPS26630_RGE0024_VQFN-24_4x4mm_P0.5mm_ThermalVias_CrtYd0.25; MPN TPS26630RGER
U102, U103, U119, U120: TLV3012B; SOT-23-6_CrtYd0.25; MPN TLV3012BIDBVR
U105: SN74LVC3G04; Texas_DCT0008A_SSOP-8_TI-land_CrtYd0.25; MPN SN74LVC3G04DCTR
U106, U110: LVC2G32; Texas_DCT0008A_SSOP-8_TI-land_CrtYd0.25; MPN SN74LVC2G32DCTR
U107: SN74LVC1G11; SOT-23-6_CrtYd0.25; MPN SN74LVC1G11DBVR
U118: LVC2G08; Texas_DCT0008A_SSOP-8_TI-land_CrtYd0.25; MPN SN74LVC2G08DCTR
W1: W1 VCHGOUT; LeadPad_PTH_D1.3mm_Pad2.3mm_CrtYd0.25
W2: W2 GND; LeadPad_PTH_D1.3mm_Pad2.3mm_CrtYd0.25
W3: W3 VCHG; LeadPad_PTH_D1.5mm_Pad2.5mm_CrtYd0.25
W4: W4 GND; LeadPad_PTH_D1.5mm_Pad2.5mm_CrtYd0.25
W6: W6 TS_EXT/GND; LeadPads_PTH_1x02_D1.0mm_Pad1.8mm_P2.54mm_Placeholder
W7: W7 SCL/GND/SDA; LeadPads_PTH_1x03_D1.0mm_Pad1.8mm_P2.54mm_Placeholder

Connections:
/3V3: C110.1, C111.1, C114.1, C115.1, C116.1, C119.1, C125.1, C126.1, C131.1, C132.1, D104.2 (K_up), D105.2 (K_up), D106.2 (K_up), R107.2, R175.2, R176.1, R177.1, R187.2, U102.6 (V+), U103.6 (V+), U105.8 (VCC), U106.8 (VCC), U107.5 (VCC), U110.8 (VCC), U118.8 (VCC), U119.6 (V+), U120.6 (V+)
/CE_DRV: R130.1, U106.7 (1Y)
/CE_DRV_J: J101.5, R130.2
/CHG_ARM: J1.11, R108.1, U105.3 (2A), U106.1 (1A)
/CHG_EFUSE_FLT: J102.9 (B4 T16), R106s.2
/CHG_IIN: C129.1, J102.2 (A2 T17), R129.2
/FCC: R122.2, R186.1, R188.1
/FCCN: U105.1 (1A), U106.5 (2A), U107.3 (B), U119.1 (OUT)
/FCCNN: U105.7 (1Y), U118.6 (2B)
/FCCP: U110.2 (1B), U118.3 (2Y)
/FCC_ON: U118.5 (2A), U120.1 (OUT)
/FCC_TAP: J102.4 (A4 T5), R122.1
/GATE: U110.5 (2A), U110.7 (1Y)
/GND: C101.2, C102a.2, C102b.2, C102c.2, C103.2, C106.2, C107.2, C108.2, C110.2, C111.2, C114.2, C115.2, C116.2, C119.2, C125.2, C126.2, C129.2, C130.2, C131.2, C132.2, D103.2 (A), D104.1 (A_lo), D105.1 (A_lo), D106.1 (A_lo), D107.2 (A), J1.4, J1.14, J1.15, J101.3, J101.9, J101.12, J101.14, J102.3 (A3 T17r), J102.8 (B3 T7b), R101.2, R104.2, R105.2, R108.2, R110.2, R112.2, R115.2, R123.2, R185.2, R189.2, U101.8 (GND), U101.15 (PGTH), U101.16 (PGOOD), U101.25 (PAD), U102.2 (V-), U103.2 (V-), U105.4 (GND), U105.6 (3A), U106.2 (1B), U106.4 (GND), U107.2 (GND), U110.4 (GND), U118.4 (GND), U119.2 (V-), U120.2 (V-), W2.1, W4.1, W6.2, W7.2
/H1: R113.1, R126.1, U102.1 (OUT), U118.1 (1A)
/H1U: U106.6 (2B), U110.1 (1A), U118.7 (1Y)
/H1_RB: J102.5 (A5 T13), R126.2
/ILIM_REL: R131A.1, R131B.1, U110.3 (2Y)
/ILIM_REL_A: J101.7, R131A.2
/ILIM_REL_B: J101.8, R131B.2
/J3V3_1: J101.1, R176.2
/J3V3_2: J101.2, R177.2
/N_DVDT: C101.1, U101.9 (dVdT)
/N_FLT: R106s.1, U101.14 (~FLT)
/N_FNP: R188.2, R189.1, U120.3 (IN+)
/N_FOM: R186.2, R187.1, U119.4 (IN-)
/N_FOP: C130.1, R184.2, R185.1, U119.3 (IN+)
/N_H1M: C107.1, D105.3 (COM), R111.2, R112.1, U102.4 (IN-)
/N_H1P: C106.1, D104.3 (COM), R109.2, R110.1, R113.2, U102.3 (IN+)
/N_ILIM: R101.1, U101.10 (ILIM)
/N_IMON: R105.1, R129.1, U101.13 (IMON)
/N_OV: R103.2, R104.1, U101.7 (OVP)
/N_UV: R102.2, R103.1, U101.6 (UVLO)
/N_UVP: C108.1, D106.3 (COM), R114.2, R115.1, R116.2, U103.3 (IN+)
/P5N: U105.5 (2Y), U107.6 (C)
/QF: U107.4 (Y), U110.6 (2B)
/QUAL: R123.1, R147.2, U107.1 (A)
/QUAL_TAP: J102.10 (B5 T10), R147.1
/REF103: U103.4 (IN-), U103.5 (REF)
/REF119: R184.1, U119.5 (REF)
/REF120: U120.4 (IN-), U120.5 (REF)
/RFC_OFF: R132.1, U106.3 (2Y)
/RFC_OFF_J: J101.10, R132.2
/SCL: J1.7, W7.1
/SDA: J1.8, W7.3
/STAT: J1.3, J101.4, R107.1
/T1_VMOT: J102.7 (B2 T1), R109.1
/T2C: J102.1 (A1 T2), R111.1, R114.1
/T6_3V3: J102.6 (B1 T6), R175.1
/TS_EXT: J1.13, W6.1
/UVB: R116.1, U103.1 (OUT), U118.2 (1B)
/VCHG: J1.18, J1.19, W3.1
/VCHGIN: C102a.1, C102b.1, C102c.1, D107.1 (K), J1.10, R102.1, U101.1 (IN), U101.2 (IN), U101.5 (IN_SYS)
/VCHGOUT: C103.1, D103.1 (K), U101.17 (OUT), U101.18 (OUT), W1.1

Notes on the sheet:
CHG header, J-TAP header, ribbon header and lead pads
Input bulk, TVS and eFuse U101 (B.4)
Comparators (B.2): H1, UVB, FCC_OFF, FCC_ON
Permit logic (B.1, B.3; 5-LVC gate, 2026-11-12)

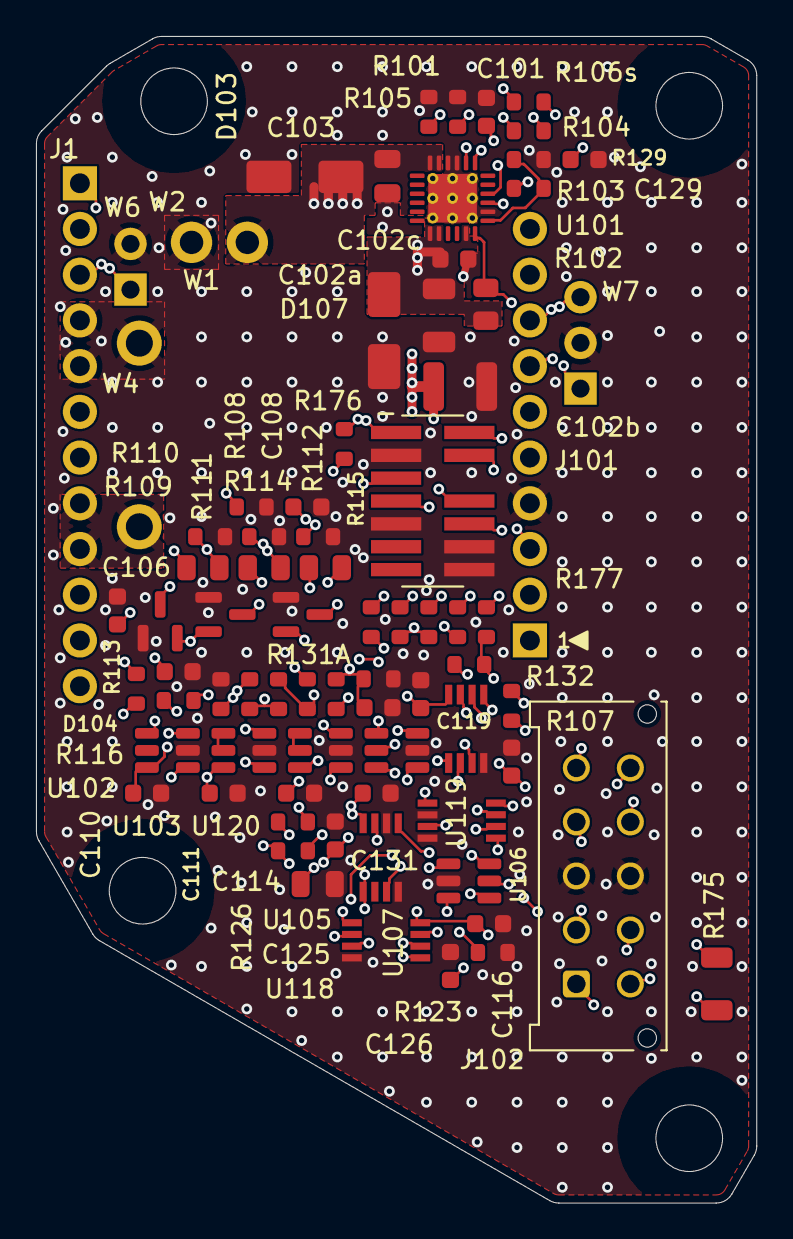
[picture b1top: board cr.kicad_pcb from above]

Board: 4 copper layers, 40.0 x 64.8 mm, 82 parts (0 on the bottom side), 54 nets.

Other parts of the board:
MH1, MH2, MH3, MH4: 6-32 hole 3.70 mm
